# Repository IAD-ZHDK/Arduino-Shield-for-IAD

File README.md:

# Arduino-Shield-for-IAD

A simple prototyping shield with Lynx Smart Servo and qwiic/stema connectors for both Ardiuino UNO and MKR board shapes.  

MKR                                                      |  UNO 
:-------------------------------------------------------:|:--------------------------------------------------------:
 |   

The arduino UNO shield uses the following pins for software serial to the LYNX smart servo connector:

rxPin 8

txPin 9

The MKR shield uses the following pins for hardware serial (SAMD21 devices) the LYNX smart servo connector: 

rxPin 1

txPin 0

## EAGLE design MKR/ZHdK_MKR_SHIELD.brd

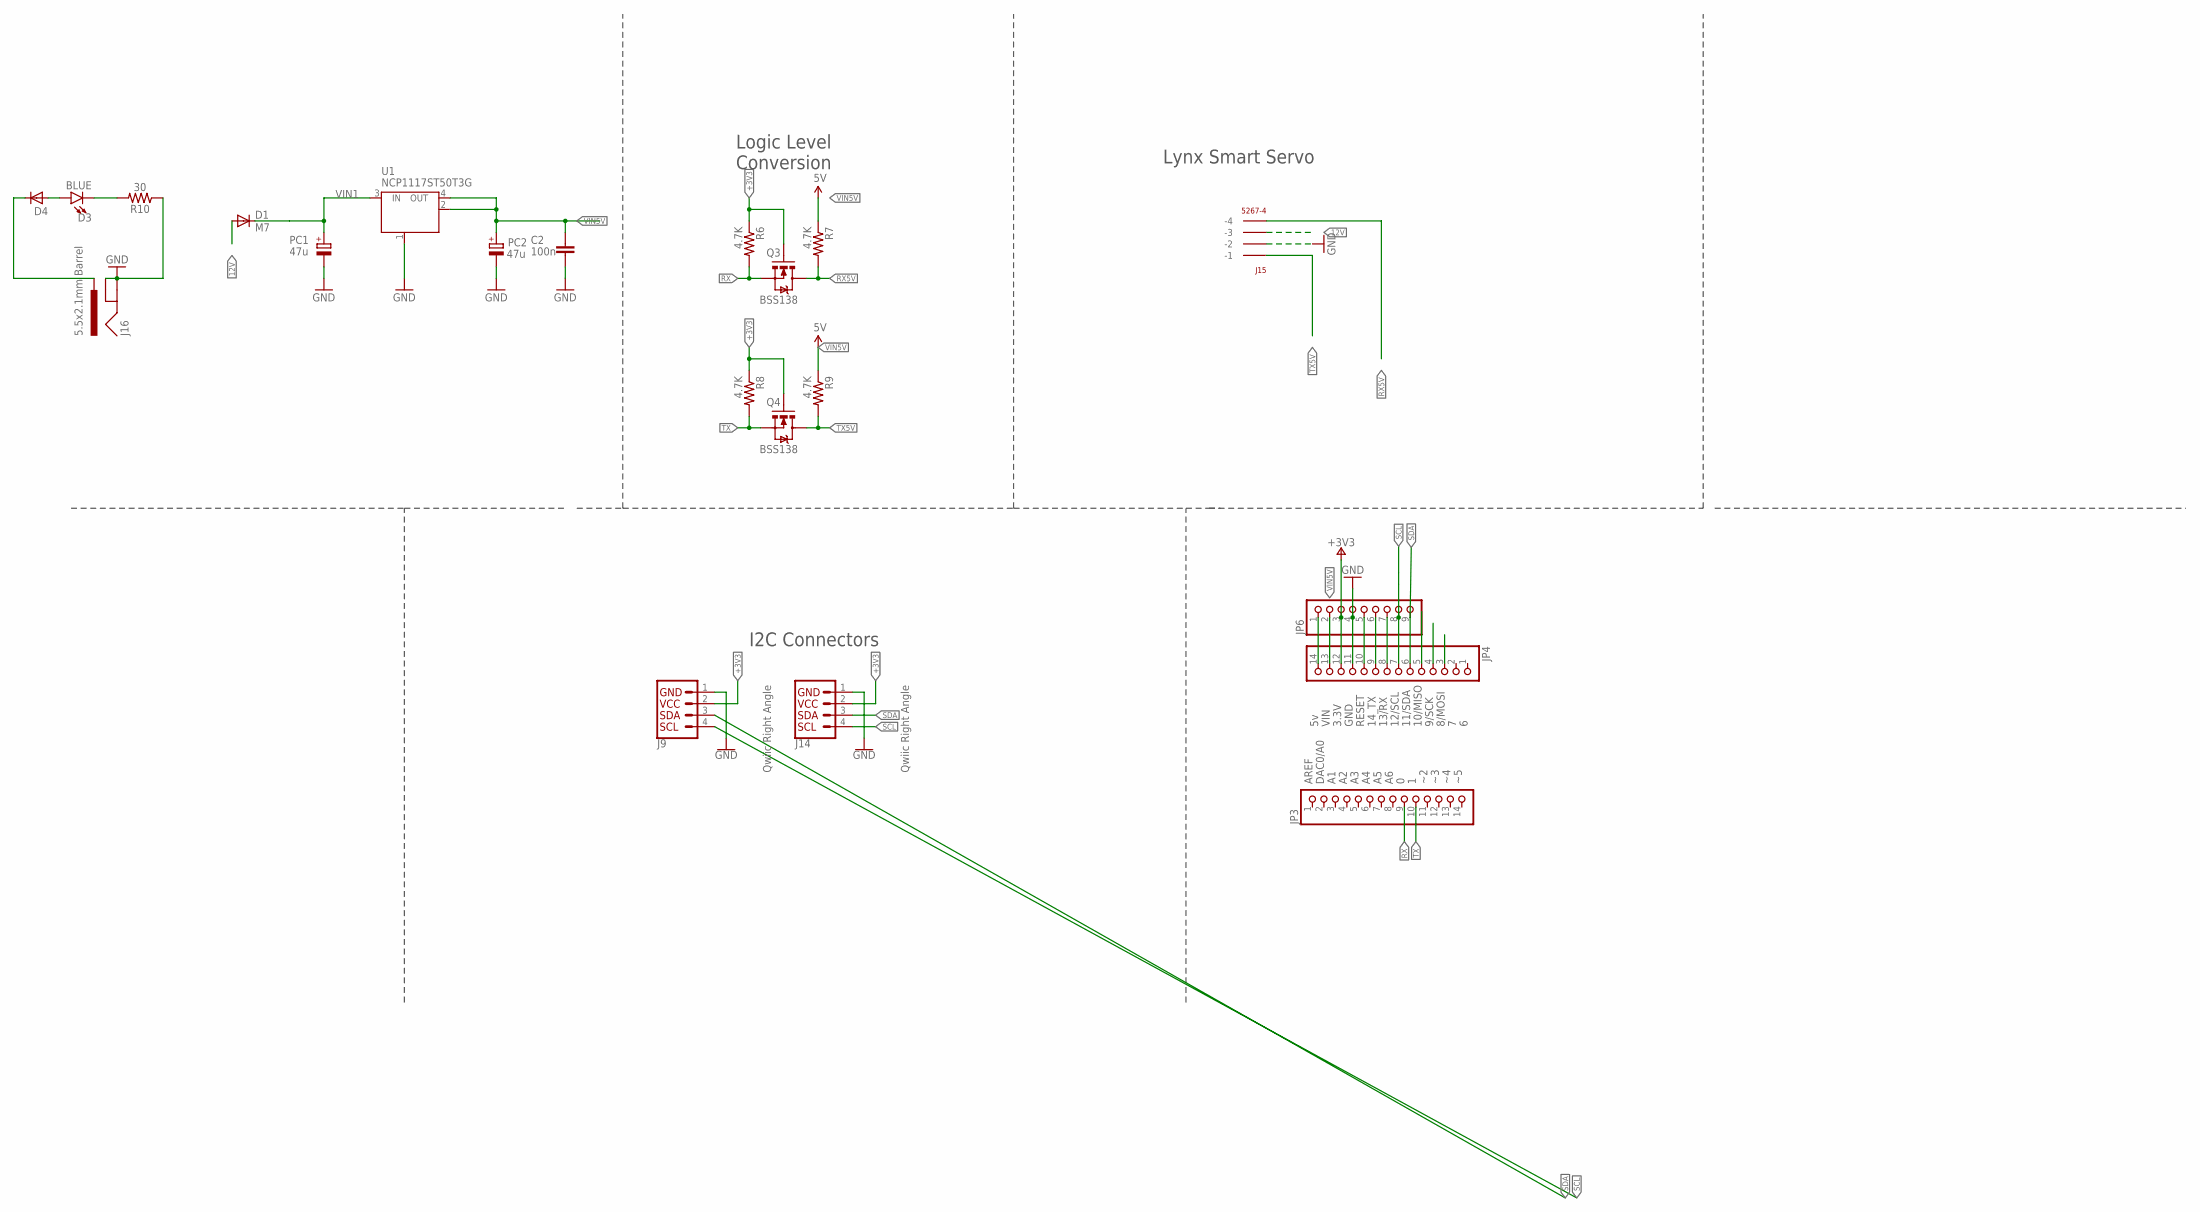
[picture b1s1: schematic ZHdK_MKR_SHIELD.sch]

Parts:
C2: 100n; C0603-ROUND
D1: M7; SMB
D3: BLUE; LED-0603
D4: 9V; SOD-123
J9, J14: Qwiic Right Angle; 1X04_1MM_RA
J15: 5267-4
J16: 5.5x2.1mm Barrel; POWER_JACK_SMD
JP3, JP4: -; 1X14
JP6: PINHD-1X9; 1X09
PC1, PC2: 47u; PANASONIC_D
Q3, Q4: BSS138; SOT23-3
R6, R7, R8, R9: 4.7K; 0603-RES
R10: 30; 0603
U1: NCP1117ST50T3G; SOT223

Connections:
12V: D1.A, D4.C, J15.P$3 (-3), J16.VIN0 (PWR)
+3V3: J9.2, J14.2, JP4.12, JP6.3, Q3.1 (G), Q4.1 (G), R6.1, R8.1
GND: C2.1, J9.1, J14.1, J15.P$2 (-2), J16.GND (GNDBREAK), J16.P$4 (GND), JP4.11, JP6.4, PC1.-, PC2.-, R10.1, U1.1 (GND/ADJ)
unnamed: JP4.14, JP6.1
unnamed: JP4.10, JP6.5
unnamed: JP4.9, JP6.6
unnamed: JP4.8, JP6.7
unnamed: D3.A, D4.A
unnamed: D3.C, R10.2
RX: JP3.9, Q3.2 (S), R6.2
RX5V: J15.P$4 (-4), Q3.3 (D), R7.2
SCL: J9.4, J14.4, JP4.7, JP6.8
SDA: J9.3, J14.3, JP4.6, JP6.9
TX: JP3.10, Q4.2 (S), R8.2
TX5V: J15.P$1 (-1), Q4.3 (D), R9.2
VIN1: D1.C, PC1.+, U1.3 (IN)
VIN5V: C2.2, JP4.13, JP6.2, PC2.+, R7.1, R9.1, U1.2 (OUT), U1.4 (OUT)

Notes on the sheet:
AREF
DAC0/A0
8/MOSI
9/SCK
10/MISO
11/SDA
12/SCL
13/RX
14_TX
RESET
GND
3.3V
VIN
Logic Level Conversion
I2C Connectors
Lynx Smart Servo

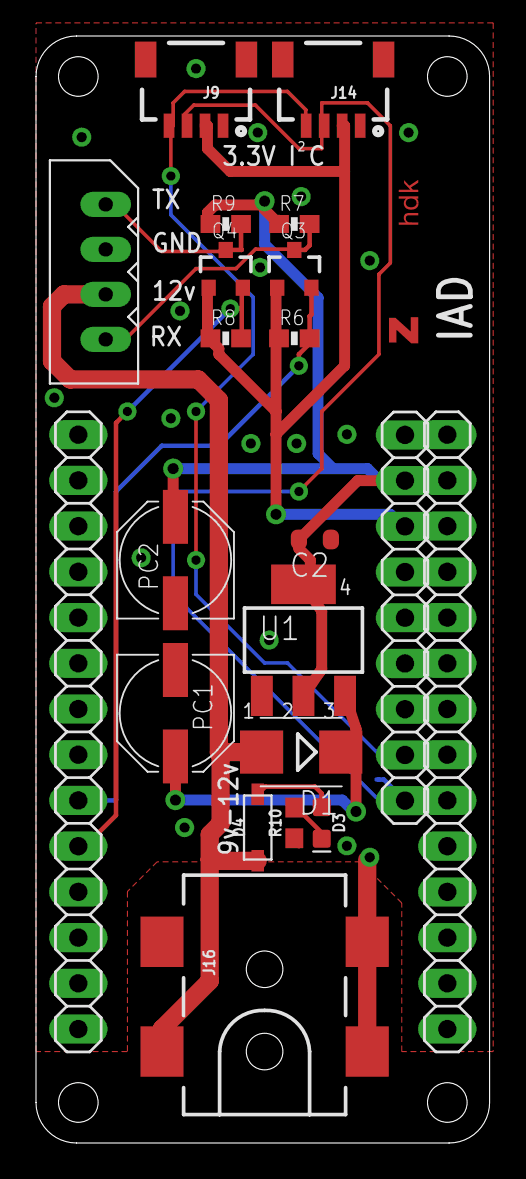
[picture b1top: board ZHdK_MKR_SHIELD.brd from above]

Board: 2 copper layers, 25.2 x 61.5 mm, 22 parts (0 on the bottom side), 17 nets.

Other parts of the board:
U$2: ZHDK_LOGO

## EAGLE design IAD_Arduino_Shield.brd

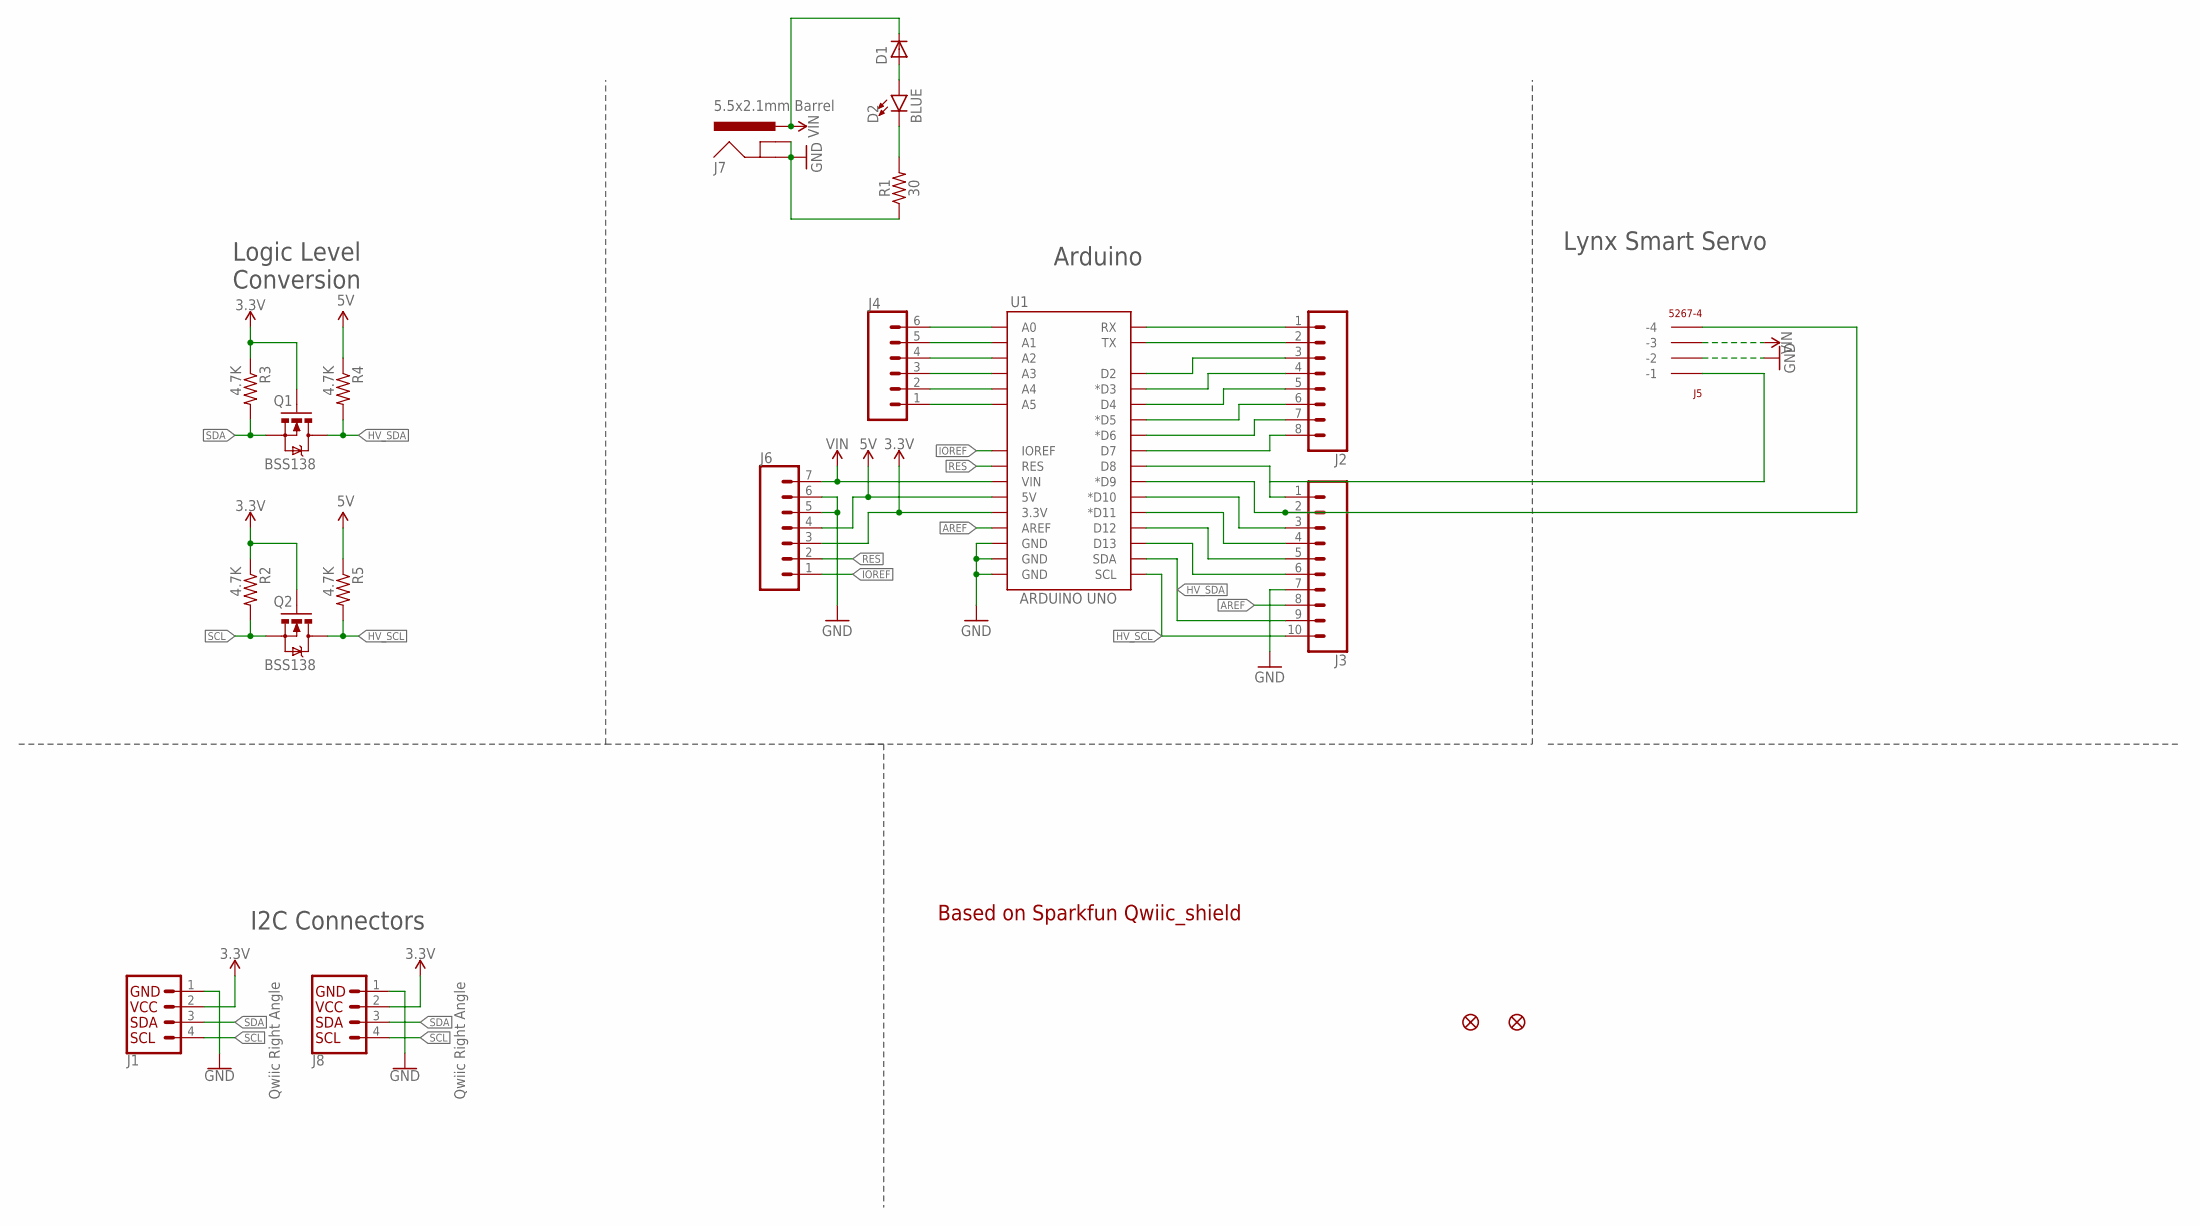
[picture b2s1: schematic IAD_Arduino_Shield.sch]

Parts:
D1: 9V; SOD-123
D2: BLUE; LED-0603
FD2, FD4: FIDUCIAL1X2; FIDUCIAL-1X2
J1, J8: Qwiic Right Angle; 1X04_1MM_RA
J2: CONN_08NO_SILK_FEMALE_PTH; 1X08_NO_SILK
J3: CONN_10NO_SILK_PTH_FEMALE; 1X10_NO_SILK
J4: CONN_06NO_SILK_FEMALE_PTH; 1X06_NO_SILK
J5: 5267-4
J6: CONN_07NO_SILK; 1X07_NO_SILK
J7: 5.5x2.1mm Barrel; POWER_JACK_SMD
Q1, Q2: BSS138; SOT23-3
R1: 30; 0603
R2, R3, R4, R5: 4.7K; 0603-RES
U1: ARDUINO UNO; UNO_R3_SHIELD_NOLABELS

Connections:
3.3V: J1.2, J6.3, J8.2, Q1.1 (G), Q2.1 (G), R2.1, R3.1, U1.3.3V
5V: J6.4, R4.1, R5.1, U1.5V
A0: J4.6, U1.A0
A1: J4.5, U1.A1
A2: J4.4, U1.A2
A3: J4.3, U1.A3
AREF: J3.8, U1.AREF
D2: J2.3, U1.D2
D3: J2.4, U1.D3 (*D3)
D4: J2.5, U1.D4
D5: J2.6, U1.D5 (*D5)
D6: J2.7, U1.D6 (*D6)
D7: J2.8, U1.D7
D8: J3.1, J5.P$1 (-1), U1.D8
D9: J3.2, J5.P$4 (-4), U1.D9 (*D9)
D10: J3.3, U1.D10 (*D10)
D11: J3.4, U1.D11 (*D11)
D12: J3.5, U1.D12
D13: J3.6, U1.D13
GND: J1.1, J3.7, J5.P$2 (-2), J6.5, J6.6, J7.GND (GNDBREAK), J7.P$4 (GND), J8.1, R1.1, U1.GND@0 (GND), U1.GND@1 (GND), U1.GND@2 (GND)
HV_SCL: J3.10, Q2.3 (D), R5.2, U1.SCL
HV_SDA: J3.9, Q1.3 (D), R4.2, U1.SDA
IOREF: J6.1, U1.IOREF
unnamed: D1.A, D2.A
unnamed: D2.C, R1.2
unnamed: J4.2, U1.A4
unnamed: J4.1, U1.A5
RES: J6.2, U1.RES
RX: J2.1, U1.RX
SCL: J1.4, J8.4, Q2.2 (S), R2.2
SDA: J1.3, J8.3, Q1.2 (S), R3.2
TX: J2.2, U1.TX
VIN: D1.C, J5.P$3 (-3), J6.7, J7.VIN0 (PWR), U1.VIN

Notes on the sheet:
Based on Sparkfun Qwiic_shield
Logic Level Conversion
Arduino
I2C Connectors
Lynx Smart Servo

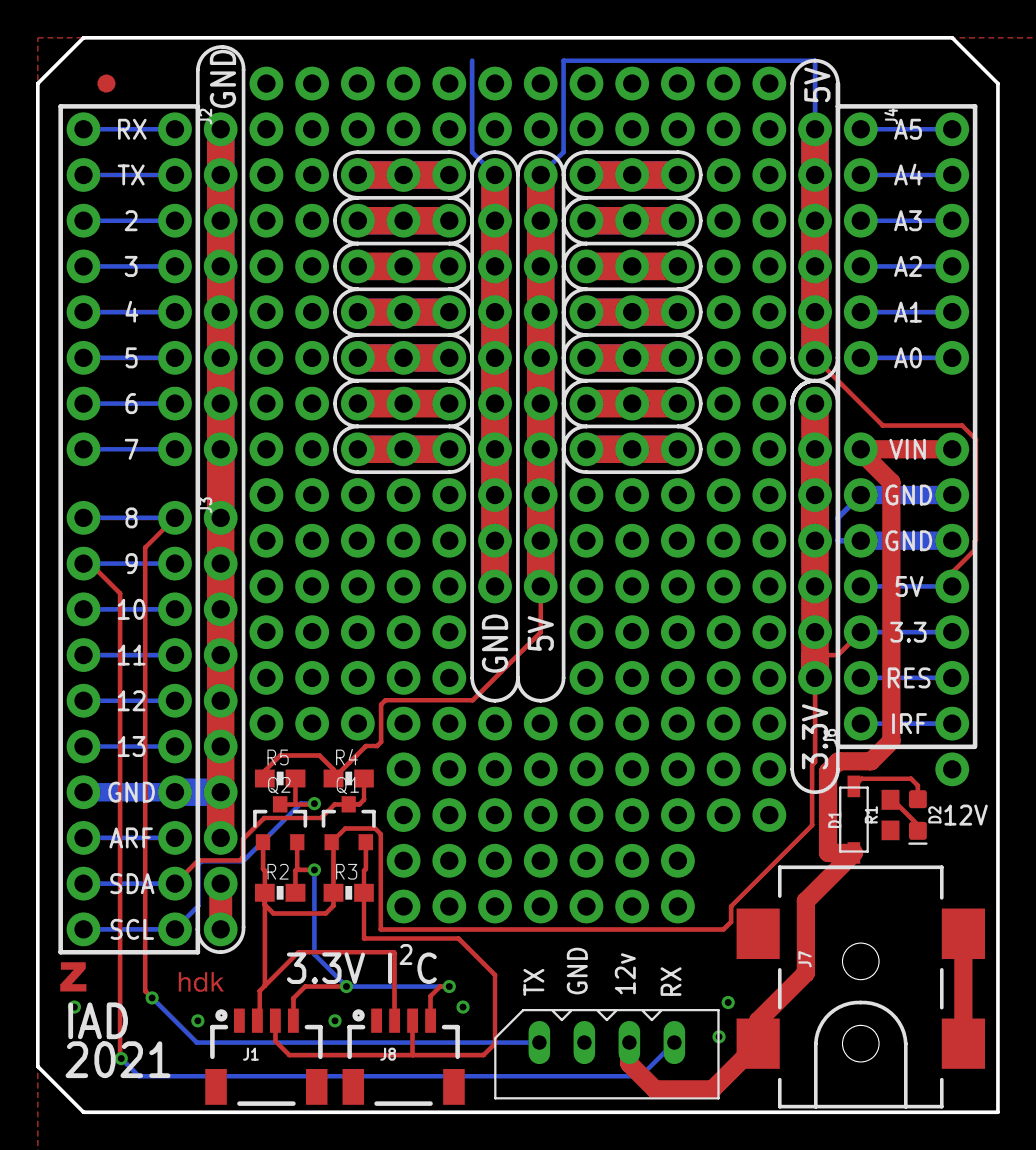
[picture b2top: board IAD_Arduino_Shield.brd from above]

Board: 2 copper layers, 53.3 x 59.7 mm, 21 parts (1 on the bottom side), 33 nets.

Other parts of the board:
U$1: ZHDK_LOGO

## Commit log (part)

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2021-10-06 Init commit
2021-10-06 fix resistor value
2023-05-03 added MKR version
2023-05-03 added arduino examples

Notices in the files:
parts and their libraries:
SparkFun-Boards: Licensing: CC v3.0 Share-Alike You are welcome to use this library for commercial purposes.
SparkFun-DiscreteSemi: Licensing: Creative Commons ShareAlike 4.0 International - https://creativecommons.org/licenses/by-sa/4.0
